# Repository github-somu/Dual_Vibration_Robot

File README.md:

# Dual_Vibration_Robot
 This repository contains files related to circuit diagrams, PCB, and 3D models
# Accessing PCB design files and Circuit diagram
Download the KiCad files folder as a .zip file and save it on your computer. After that, extract the folder. Then, the files will open appropriately in KiCad software.

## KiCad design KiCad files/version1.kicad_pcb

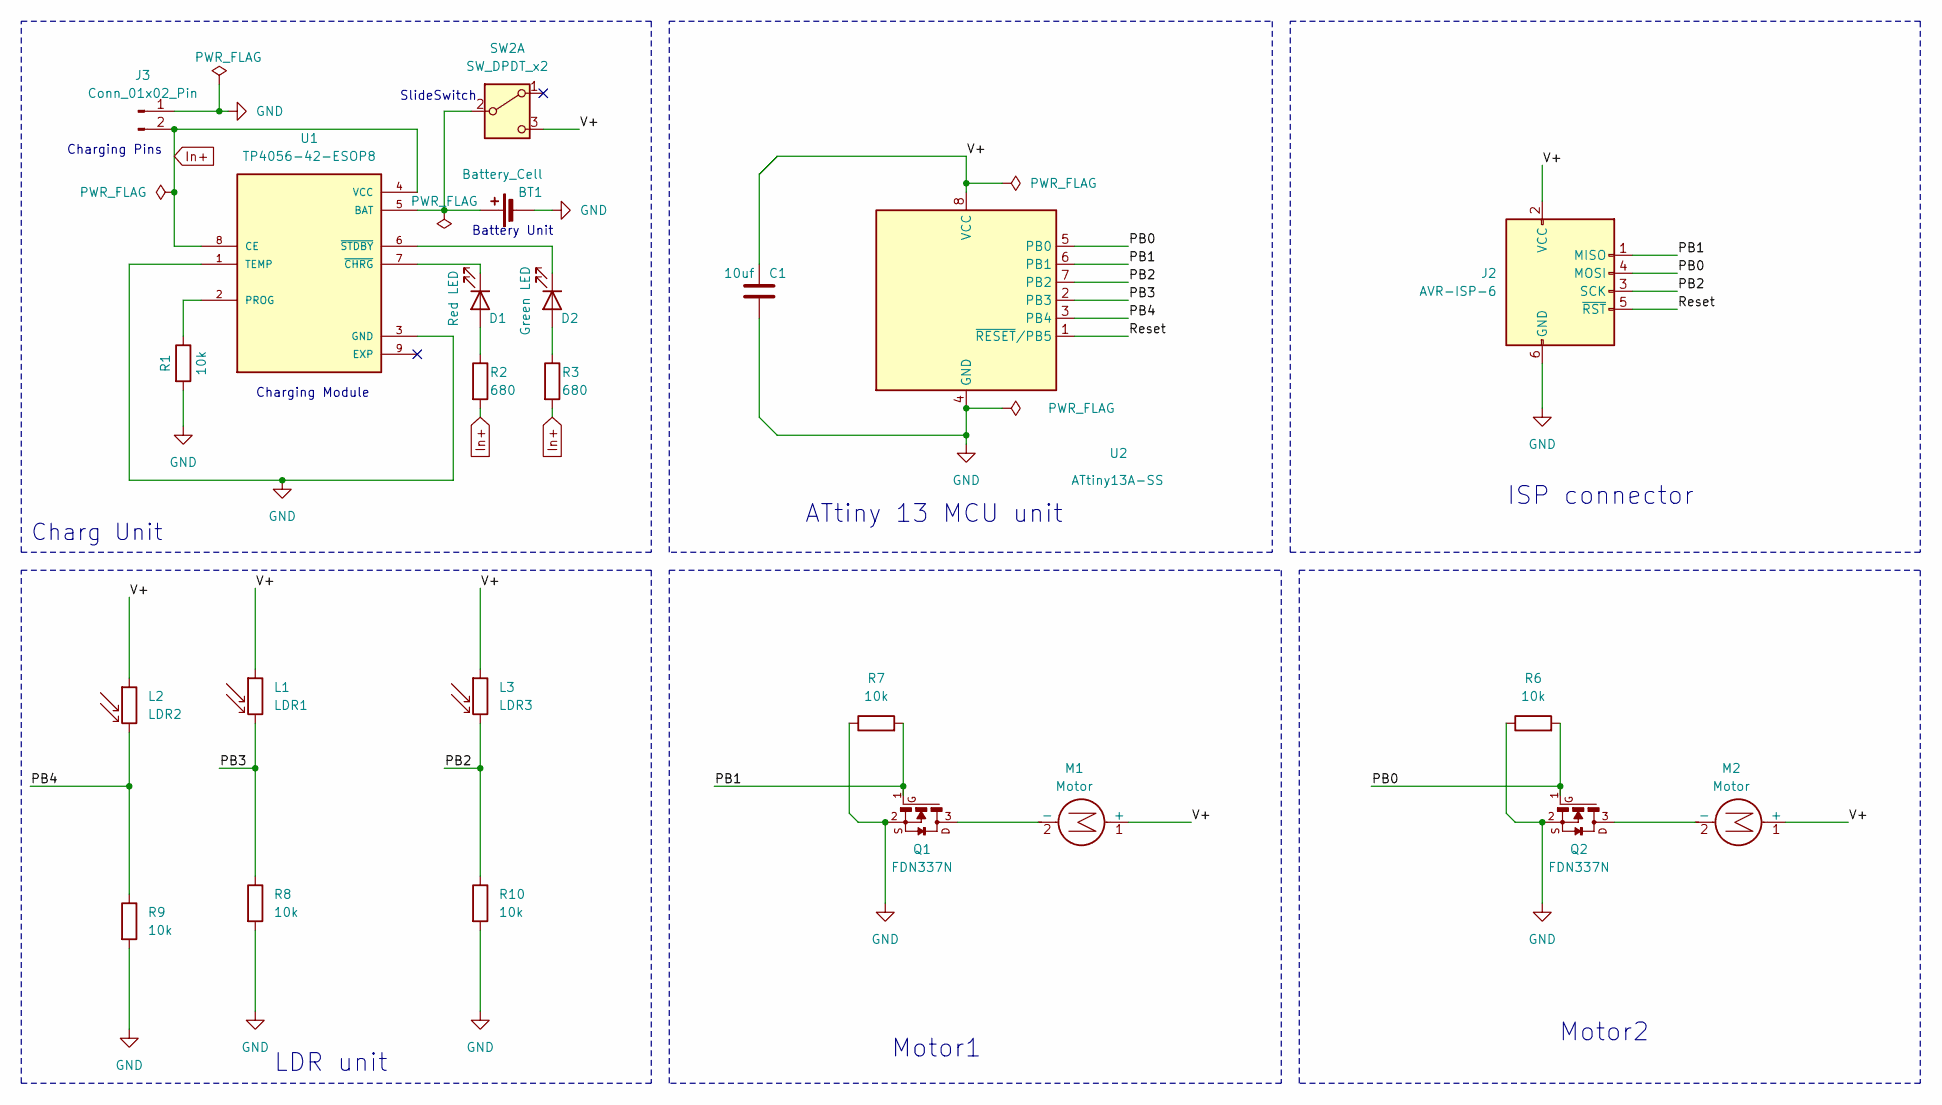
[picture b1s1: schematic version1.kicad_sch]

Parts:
BT1: Battery_Cell; BatteryHolder_KP401020
C1: 10uf; C_0805_2012Metric_Pad1.18x1.45mm_HandSolder
D1: Red LED; LED_0805_2012Metric_Pad1.15x1.40mm_HandSolder
D2: Green LED; LED_0805_2012Metric_Pad1.15x1.40mm_HandSolder
J2: AVR-ISP-6; IDC-Header_2x03_P2.54mm_Vertical
J3: Conn_01x02_Pin; PinHeader_1x02_P2.54mm_Vertical
L1: LDR1; R_LDR_5.1x4.3mm_P3.4mm_Vertical
L2: LDR2; R_LDR_5.1x4.3mm_P3.4mm_Vertical
L3: LDR3; R_LDR_5.1x4.3mm_P3.4mm_Vertical
M1, M2: Motor; VibrationMotor
Q1, Q2: FDN337N; SSOT-3
R1, R6, R7, R8, R9, R10: 10k; R_0805_2012Metric_Pad1.20x1.40mm_HandSolder
R2, R3: 680; R_0805_2012Metric_Pad1.20x1.40mm_HandSolder
SW2: SW_DPDT_x2; Switch
U1: TP4056-42-ESOP8; SOIC127P600X175-9N; PARTREV NA
U2: ATtiny13A-SS; SOIC127P798X216-8N

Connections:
/PB0: J2.4 (MOSI), Q2.1, R6.2, U2.5 (PB0)
/PB1: J2.1 (MISO), Q1.1, R7.2, U2.6 (PB1)
/PB2: J2.3 (SCK), L3.2, R10.1, U2.7 (PB2)
/PB3: L1.2, R8.1, U2.2 (PB3)
/PB4: L2.2, R9.1, U2.3 (PB4)
/Reset: J2.5 (~RST), U2.1 (~RESET/PB5)
/V+: C1.1, J2.2 (VCC), L1.1, L2.1, L3.1, M1.1 (+), M2.1 (+), SW2.3 (C), U2.8 (VCC)
GND: BT1.2 (-), C1.2, J2.6 (GND), J3.1, Q1.2, Q2.2, R1.2, R6.1, R7.1, R8.2, R9.2, R10.2, U1.1 (TEMP), U1.3 (GND), U2.4 (GND)
In+: J3.2, R2.2, R3.2, U1.4 (VCC), U1.8 (CE)
unnamed: BT1.1 (+), SW2.2 (B), U1.5 (BAT)
unnamed: D1.2 (A), R2.1
unnamed: D1.1 (K), U1.7 (~CHRG)
unnamed: D2.2 (A), R3.1
unnamed: D2.1 (K), U1.6 (~STDBY)
unnamed: M1.2 (-), Q1.3
unnamed: M2.2 (-), Q2.3
unnamed: R1.1, U1.2 (PROG)

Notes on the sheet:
ISP connector
Charg Unit
Motor2
ATtiny 13 MCU unit
LDR unit
Charging Module
SlideSwitch
Battery Unit
Motor1
Charging Pins

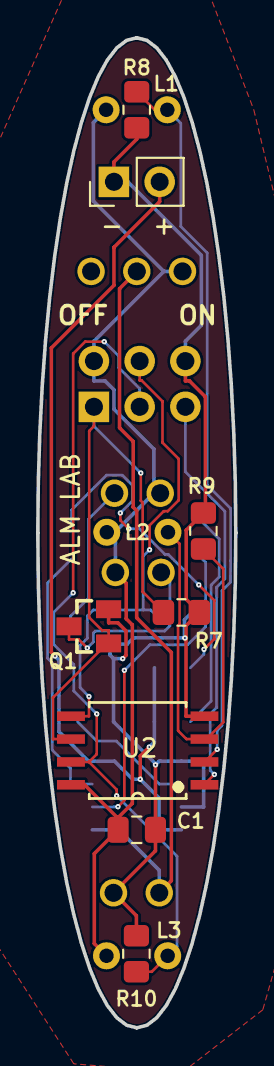
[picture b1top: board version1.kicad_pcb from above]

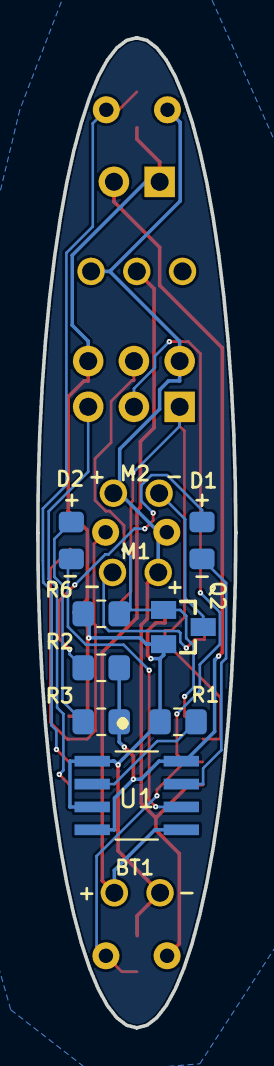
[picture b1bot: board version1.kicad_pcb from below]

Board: 2 copper layers, 11.0 x 55.0 mm, 24 parts (10 on the bottom side), 17 nets.

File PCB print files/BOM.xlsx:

Sample - Bill of Material
Sr. No. | Quantity | Reference | Value | Part Type | PCB Footprint | Manufacturer Part Number/ Generic Part Number[PCB Power] | Manufacturer Name | Description
1 | 5 | R1, R7, R8, R9, R10 | 10 komh, 125mW | Resistor | SMD0805 | GPR080510K | Generic Components - PCB Power | SMD Chip Resistor, 10 kohm, ± 1%, 125 mW, 0805 [2012 Metric], Thick Film, Gener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
2 | 2 | R2, R3 | 4.7 komh, 125mW | Resistor | SMD0805 | GPR08054K7 | Generic Components - PCB Power | SMD Chip Resistor, 4.7 kohm, ± 1%, 125 mW, 0805 [2012 Metric], Thick Film, Gene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
3 | 1 | C1 | 10uF, 35V | Capacitor | SMD0805 | GPC0805106-35 | Generic Components - PCB Power | Multilayer Ceramic Capacitors MLCC - SMD/SMT Multilayer Ceramic Capacitors MLCC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
4 | 1 | U2 | NA | ATtiny13A | SOIC127P798X216-8N | ATtiny13A-SU / ATtiny13A-SUR / ATtiny13A-SH / ATtiny13A-SHR | Microchip Technology | 8-bit Microcontrollers - MCU 1KB In-system Flash 20MHz 1.8V-5.5V
5 | 1 | Q2 | NA | n-MOSFET | SSOT-3 | FDN337N | onsemi / Fairchild | MOSFET SSOT-3 N-CH 30V
6 | 1 | D2 | NA | LED-G | SMD0805 | HSMM-C170 | Broadcom / Avago | Standard LEDs - SMD Green Diffused 525nm 120mcd
7 | 1 | D1 | NA | LED-R | SMD0805 | HSMH-H170 | Broadcom / Avago | Standard LEDs - SMD 0805 Top Mount Mono-Color ChipLED, AllnGaP Red
8 | 1 | U1 | NA | Battery Charging IC | SOIC127P600X175-9N | TP4056-42-ESOP8 | TOPPOWER(Nanjing Extension Microelectronics) | ESOP-8 Battery Management ICs ROHS

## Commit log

2025-03-28 Added the 3D model files
2025-03-28 Added the KiCad files
2025-03-28 Added PCB print files
2025-04-11 updated files
